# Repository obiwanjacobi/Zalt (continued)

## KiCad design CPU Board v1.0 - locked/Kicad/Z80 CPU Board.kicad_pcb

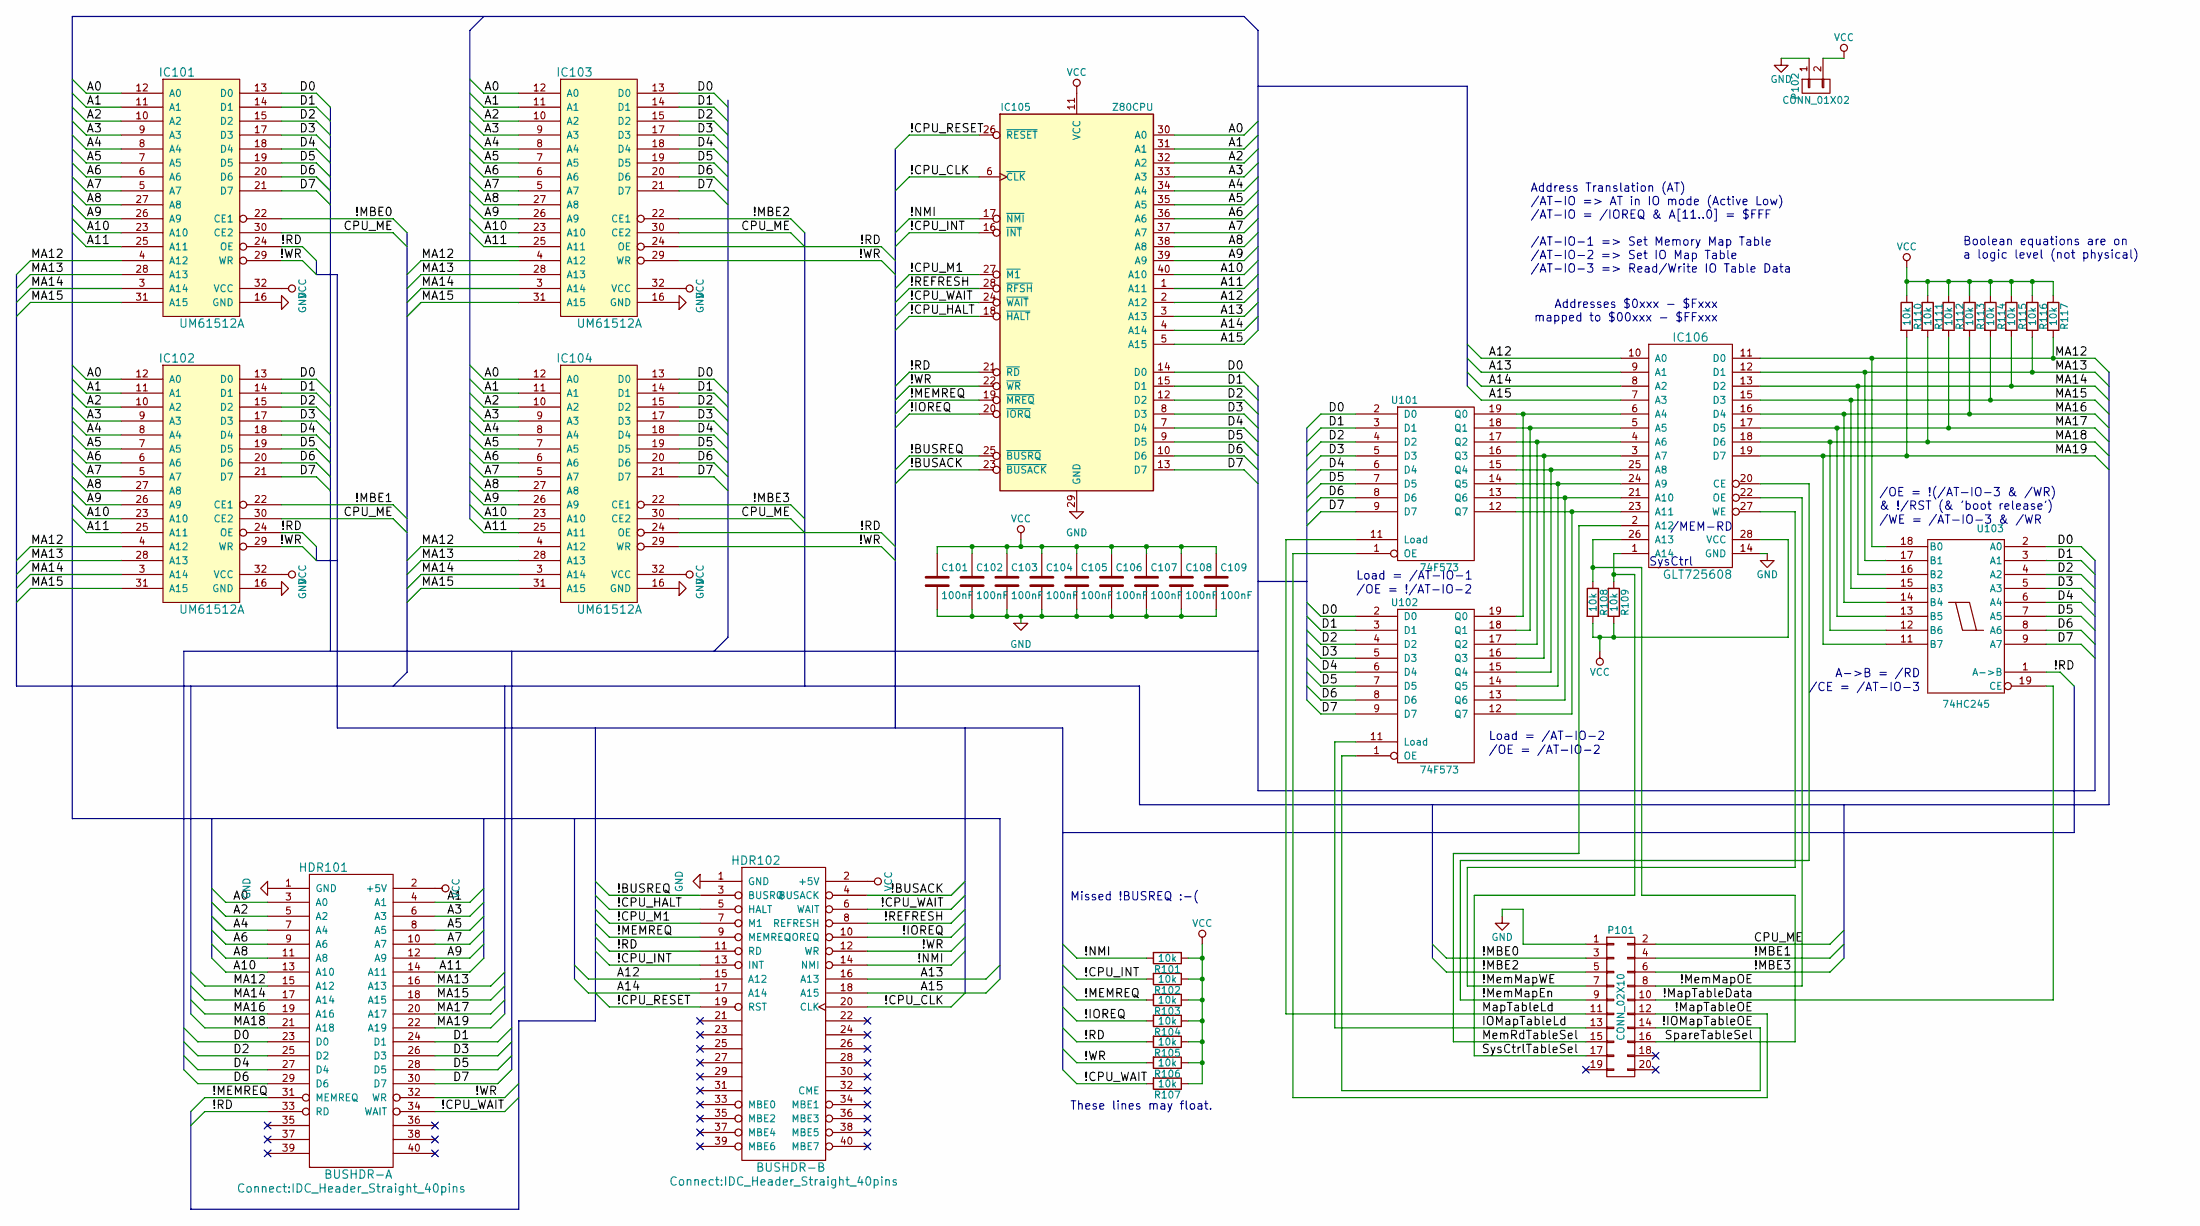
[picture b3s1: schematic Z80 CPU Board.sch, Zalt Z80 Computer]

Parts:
C101, C102, C103, C104, C105, C106, C107, C108, C109: 100nF; C_0603_HandSoldering
HDR101: BUSHDR-A; IDC_Header_Straight_40pins
HDR102: BUSHDR-B; IDC_Header_Straight_40pins
IC101, IC102, IC103, IC104: UM61512A; DIP-32_0_ELL
IC105: Z80CPU; DIP-40_W15.24mm_LongPads
IC106: GLT725608; SOIC-28_7.5x17.9mm_Pitch1.27mm
P101: CONN_02X10; Pin_Header_Straight_2x10
P102: CONN_01X02; PINHEAD1-2
R101, R102, R103, R104, R105, R106, R107, R108, R109, R110, R111, R112, R113, R114, R115, R116, R117: 10k; R_0603_HandSoldering
U101, U102: 74F573; DIP-20_W7.62mm_LongPads
U103: 74HC245; DIP-20_W7.62mm_LongPads

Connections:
/!BUSACK: HDR102.4 (BUSACK), IC105.23 (~BUSACK~)
/!BUSREQ: HDR102.3 (BUSRQ), IC105.25 (~BUSRQ~)
/!CPU_CLK: HDR102.20 (CLK), IC105.6 (~CLK~)
/!CPU_HALT: HDR102.5 (HALT), IC105.18 (~HALT~)
/!CPU_INT: HDR102.13 (INT), IC105.16 (~INT~), R102.2
/!CPU_M1: HDR102.7 (M1), IC105.27 (~M1~)
/!CPU_RESET: HDR102.19 (RST), IC105.26 (~RESET~)
/!CPU_WAIT: HDR101.34 (WAIT), HDR102.6 (WAIT), IC105.24 (~WAIT~), R107.2
/!IOMapTableOE: P101.14, U102.1 (OE)
/!IOREQ: HDR102.10 (IOREQ), IC105.20 (~IORQ~), R104.2
/!MBE0: IC101.22 (CE1), P101.3
/!MBE1: IC102.22 (CE1), P101.4
/!MBE2: IC103.22 (CE1), P101.5
/!MBE3: IC104.22 (CE1), P101.6
/!MEMREQ: HDR101.31 (MEMREQ), HDR102.9 (MEMREQ), IC105.19 (~MREQ~), R103.2
/!MapTableData: P101.10, U103.19 (CE)
/!MapTableOE: P101.12, U101.1 (OE)
/!MemMapEn: IC106.27 (WE), P101.7
/!MemMapOE: IC106.22 (OE), P101.8
/!MemMapWE: IC106.20 (CE), P101.9
/!NMI: HDR102.14 (NMI), IC105.17 (~NMI~), R101.2
/!RD: HDR101.33 (RD), HDR102.11 (RD), IC101.24 (OE), IC102.24 (OE), IC103.24 (OE), IC104.24 (OE), IC105.21 (~RD~), R105.2, U103.1 (A->B)
/!REFRESH: HDR102.8 (REFRESH), IC105.28 (~RFSH~)
/!WR: HDR101.32 (WR), HDR102.12 (WR), IC101.29 (WR), IC102.29 (WR), IC103.29 (WR), IC104.29 (WR), IC105.22 (~WR~), R106.2
/A0: HDR101.3 (A0), IC101.12 (A0), IC102.12 (A0), IC103.12 (A0), IC104.12 (A0), IC105.30 (A0)
/A1: HDR101.4 (A1), IC101.11 (A1), IC102.11 (A1), IC103.11 (A1), IC104.11 (A1), IC105.31 (A1)
/A2: HDR101.5 (A2), IC101.10 (A2), IC102.10 (A2), IC103.10 (A2), IC104.10 (A2), IC105.32 (A2)
/A3: HDR101.6 (A3), IC101.9 (A3), IC102.9 (A3), IC103.9 (A3), IC104.9 (A3), IC105.33 (A3)
/A4: HDR101.7 (A4), IC101.8 (A4), IC102.8 (A4), IC103.8 (A4), IC104.8 (A4), IC105.34 (A4)
/A5: HDR101.8 (A5), IC101.7 (A5), IC102.7 (A5), IC103.7 (A5), IC104.7 (A5), IC105.35 (A5)
/A6: HDR101.9 (A6), IC101.6 (A6), IC102.6 (A6), IC103.6 (A6), IC104.6 (A6), IC105.36 (A6)
/A7: HDR101.10 (A7), IC101.5 (A7), IC102.5 (A7), IC103.5 (A7), IC104.5 (A7), IC105.37 (A7)
/A8: HDR101.11 (A8), IC101.27 (A8), IC102.27 (A8), IC103.27 (A8), IC104.27 (A8), IC105.38 (A8)
/A9: HDR101.12 (A9), IC101.26 (A9), IC102.26 (A9), IC103.26 (A9), IC104.26 (A9), IC105.39 (A9)
/A10: HDR101.13 (A10), IC101.23 (A10), IC102.23 (A10), IC103.23 (A10), IC104.23 (A10), IC105.40 (A10)
/A11: HDR101.14 (A11), IC101.25 (A11), IC102.25 (A11), IC103.25 (A11), IC104.25 (A11), IC105.1 (A11)
/A12: HDR102.15 (A12), IC105.2 (A12), IC106.10 (A0)
/A13: HDR102.16 (A13), IC105.3 (A13), IC106.9 (A1)
/A14: HDR102.17 (A14), IC105.4 (A14), IC106.8 (A2)
/A15: HDR102.18 (A15), IC105.5 (A15), IC106.7 (A3)
/CPU_ME: IC101.30 (CE2), IC102.30 (CE2), IC103.30 (CE2), IC104.30 (CE2), P101.2
/D0: HDR101.23 (D0), IC101.13 (D0), IC102.13 (D0), IC103.13 (D0), IC104.13 (D0), IC105.14 (D0), U101.2 (D0), U102.2 (D0), U103.2 (A0)
/D1: HDR101.24 (D1), IC101.14 (D1), IC102.14 (D1), IC103.14 (D1), IC104.14 (D1), IC105.15 (D1), U101.3 (D1), U102.3 (D1), U103.3 (A1)
/D2: HDR101.25 (D2), IC101.15 (D2), IC102.15 (D2), IC103.15 (D2), IC104.15 (D2), IC105.12 (D2), U101.4 (D2), U102.4 (D2), U103.4 (A2)
/D3: HDR101.26 (D3), IC101.17 (D3), IC102.17 (D3), IC103.17 (D3), IC104.17 (D3), IC105.8 (D3), U101.5 (D3), U102.5 (D3), U103.5 (A3)
/D4: HDR101.27 (D4), IC101.18 (D4), IC102.18 (D4), IC103.18 (D4), IC104.18 (D4), IC105.7 (D4), U101.6 (D4), U102.6 (D4), U103.6 (A4)
/D5: HDR101.28 (D5), IC101.19 (D5), IC102.19 (D5), IC103.19 (D5), IC104.19 (D5), IC105.9 (D5), U101.7 (D5), U102.7 (D5), U103.7 (A5)
/D6: HDR101.29 (D6), IC101.20 (D6), IC102.20 (D6), IC103.20 (D6), IC104.20 (D6), IC105.10 (D6), U101.8 (D6), U102.8 (D6), U103.8 (A6)
/D7: HDR101.30 (D7), IC101.21 (D7), IC102.21 (D7), IC103.21 (D7), IC104.21 (D7), IC105.13 (D7), U101.9 (D7), U102.9 (D7), U103.9 (A7)
/IOMapTableLd: P101.13, U102.11 (Load)
/MA12: HDR101.15 (A12), IC101.4 (A12), IC102.4 (A12), IC103.4 (A12), IC104.4 (A12), IC106.11 (D0), R117.2, U103.18 (B0)
/MA13: HDR101.16 (A13), IC101.28 (A13), IC102.28 (A13), IC103.28 (A13), IC104.28 (A13), IC106.12 (D1), R116.2, U103.17 (B1)
/MA14: HDR101.17 (A14), IC101.3 (A14), IC102.3 (A14), IC103.3 (A14), IC104.3 (A14), IC106.13 (D2), R115.2, U103.16 (B2)
/MA15: HDR101.18 (A15), IC101.31 (A15), IC102.31 (A15), IC103.31 (A15), IC104.31 (A15), IC106.15 (D3), R114.2, U103.15 (B3)
/MA16: HDR101.19 (A16), IC106.16 (D4), R113.2, U103.14 (B4)
/MA17: HDR101.20 (A17), IC106.17 (D5), R112.2, U103.13 (B5)
/MA18: HDR101.21 (A18), IC106.18 (D6), R111.2, U103.12 (B6)
/MA19: HDR101.22 (A19), IC106.19 (D7), R110.2, U103.11 (B7)
/MapTableLd: P101.11, U101.11 (Load)
/MemRdTableSel: IC106.2 (A12), P101.15
/SpareTableSel: IC106.26 (A13), P101.16, R108.1
/SysCtrlTableSel: IC106.1 (A14), P101.17, R109.1
GND: C101.2, C102.2, C103.2, C104.2, C105.2, C106.2, C107.2, C108.2, C109.2, HDR101.1 (GND), HDR102.1 (GND), IC101.16 (GND), IC102.16 (GND), IC103.16 (GND), IC104.16 (GND), IC105.29 (GND), IC106.14 (GND), P101.1, P102.1, U101.10 (GND), U102.10 (GND), U103.10 (GND)
unnamed: IC106.3 (A7), U101.16 (Q3), U102.16 (Q3)
unnamed: IC106.4 (A6), U101.17 (Q2), U102.17 (Q2)
unnamed: IC106.5 (A5), U101.18 (Q1), U102.18 (Q1)
unnamed: IC106.6 (A4), U101.19 (Q0), U102.19 (Q0)
unnamed: IC106.21 (A10), U101.13 (Q6), U102.13 (Q6)
unnamed: IC106.23 (A11), U101.12 (Q7), U102.12 (Q7)
unnamed: IC106.24 (A9), U101.14 (Q5), U102.14 (Q5)
unnamed: IC106.25 (A8), U101.15 (Q4), U102.15 (Q4)
VCC: C101.1, C102.1, C103.1, C104.1, C105.1, C106.1, C107.1, C108.1, C109.1, HDR101.2 (+5V), HDR102.2 (+5V), IC101.32 (VCC), IC102.32 (VCC), IC103.32 (VCC), IC104.32 (VCC), IC105.11 (VCC), IC106.28 (VCC), P102.2, R101.1, R102.1, R103.1, R104.1, R105.1, R106.1, R107.1, R108.2, R109.2, R110.1, R111.1, R112.1, R113.1, R114.1, R115.1, R116.1, R117.1, U101.20 (VCC), U102.20 (VCC), U103.20 (VCC)

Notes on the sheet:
Addresses $0xxx - $Fxxx mapped to $00xxx - $FFxxx
Address Translation (AT) /AT-IO => AT in IO mode (Active Low) /AT-IO = /IOREQ & A[11..0] = $FFF /AT-IO-1 => Set Memory Map Table /AT-IO-2 => Set IO Map Table /AT-IO-3 => Read/Write IO Table Data
A->B = /RD
/CE = /AT-IO-3
/OE = !(/AT-IO-3 & /WR) & !/RST (& 'boot release')
/WE = /AT-IO-3 & /WR
/MEM-RD
SysCtrl
Load = /AT-IO-2
/OE = /AT-IO-2
Boolean equations are on a logic level (not physical)
Load = /AT-IO-1
/OE = !/AT-IO-2
These lines may float.
Missed !BUSREQ :-(

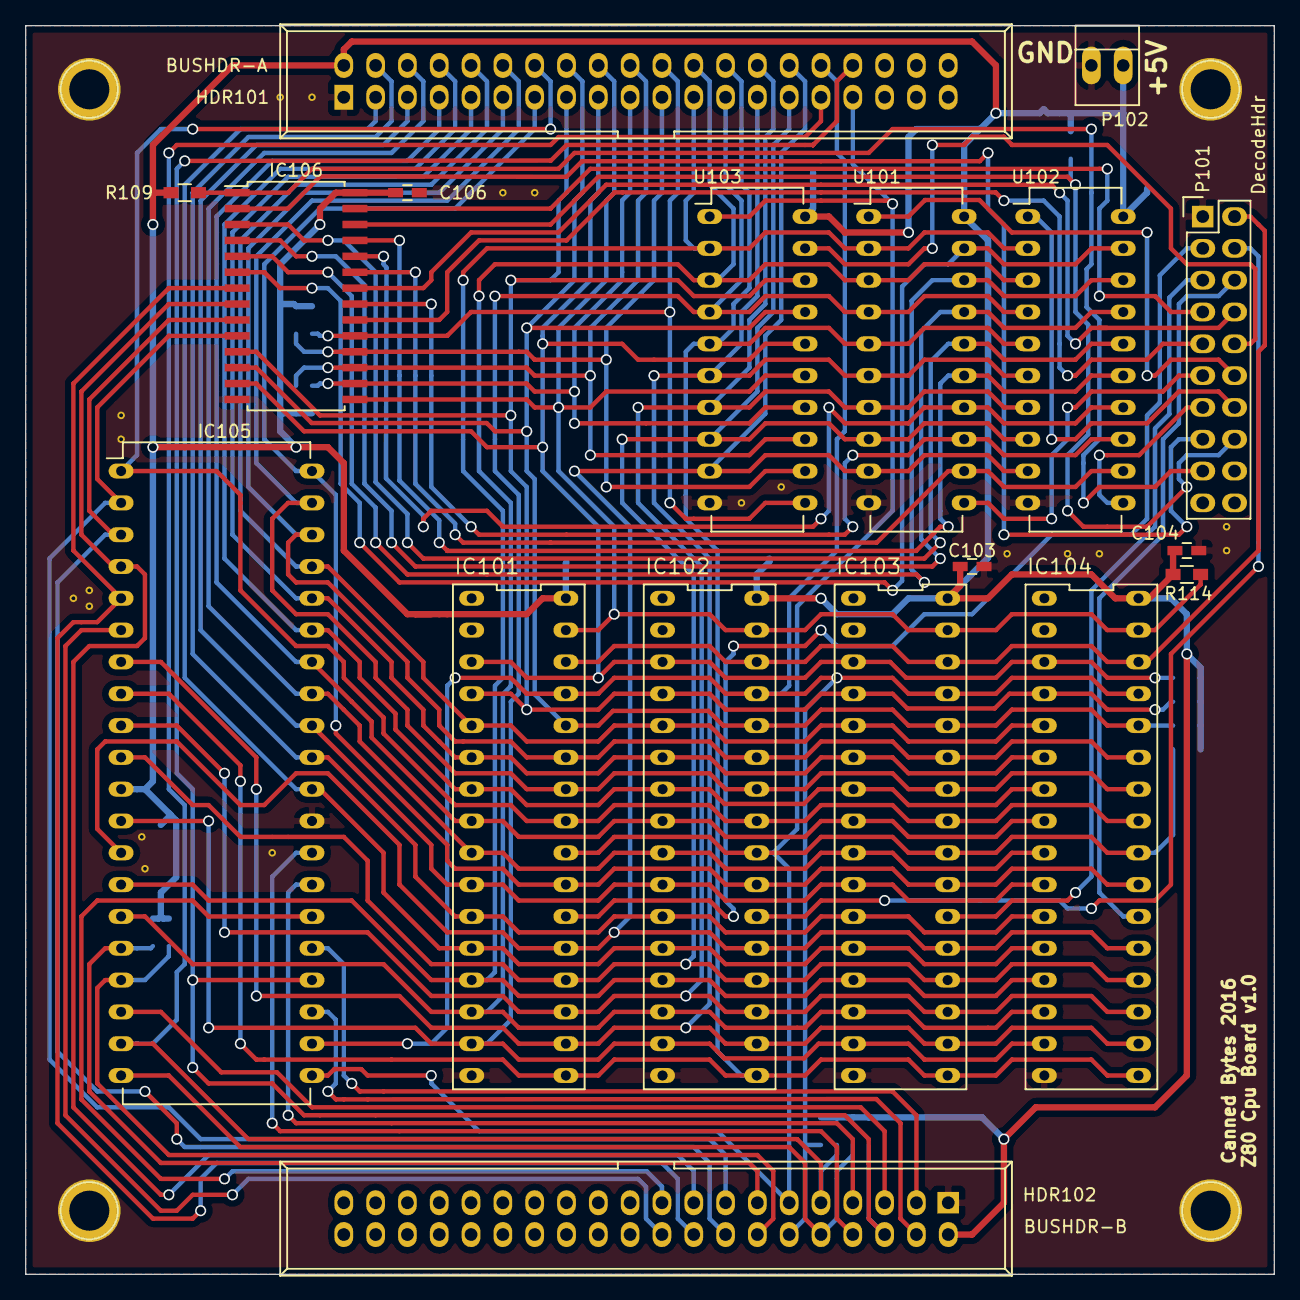
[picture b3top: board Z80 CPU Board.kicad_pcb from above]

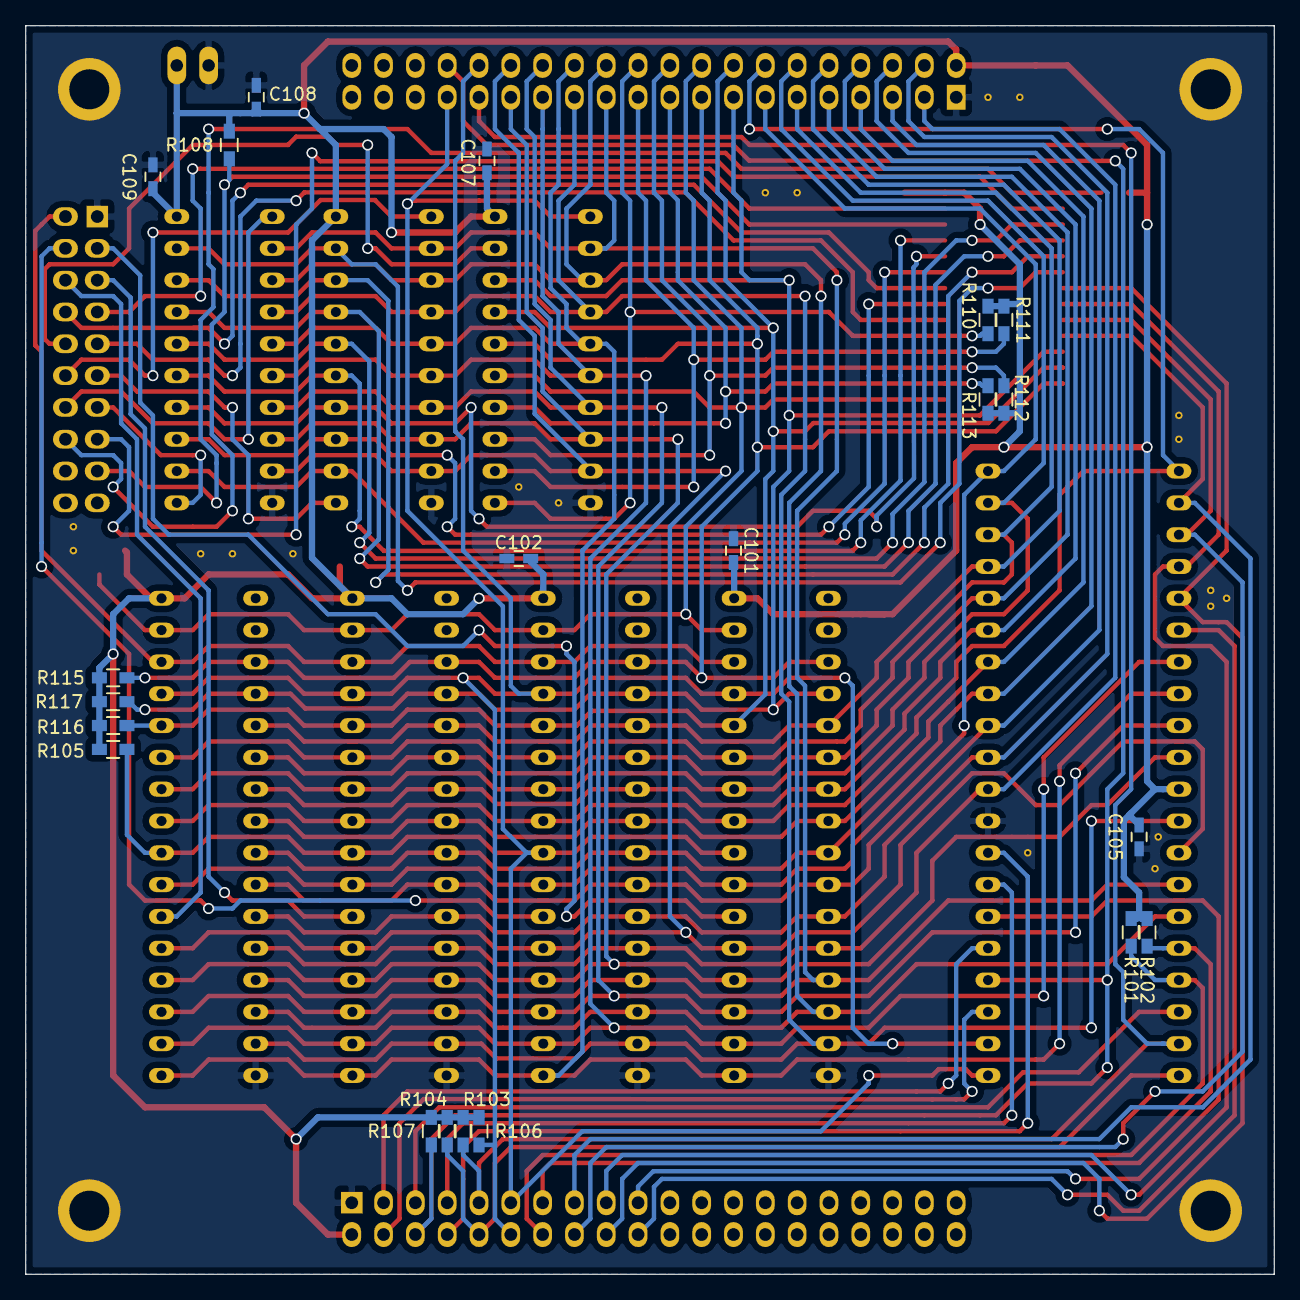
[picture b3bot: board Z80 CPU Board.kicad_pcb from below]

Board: 2 copper layers, 99.7 x 99.7 mm, 39 parts (21 on the bottom side), 72 nets.

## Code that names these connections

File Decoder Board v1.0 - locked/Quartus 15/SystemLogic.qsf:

# -------------------------------------------------------------------------- #
#
# Copyright (C) 1991-2015 Altera Corporation. All rights reserved.
# Your use of Altera Corporation's design tools, logic functions 
# and other software and tools, and its AMPP partner logic 
# functions, and any output files from any of the foregoing 
# (including device programming or simulation files), and any 
# associated documentation or information are expressly subject 
# to the terms and conditions of the Altera Program License 
# Subscription Agreement, the Altera Quartus Prime License Agreement,
# the Altera MegaCore Function License Agreement, or other 
# applicable license agreement, including, without limitation, 
# that your use is for the sole purpose of programming logic 
# devices manufactured by Altera and sold by Altera or its 
# authorized distributors.  Please refer to the applicable 
# agreement for further details.
#
# -------------------------------------------------------------------------- #
#
# Quartus Prime
# Version 15.1.0 Build 185 10/21/2015 SJ Lite Edition
# Date created = 08:41:50  December 29, 2015
#
# -------------------------------------------------------------------------- #
#
# Notes:
#
# 1) The default values for assignments are stored in the file:
#		SystemLogic_assignment_defaults.qdf
#    If this file doesn't exist, see file:
#		assignment_defaults.qdf
#
# 2) Altera recommends that you do not modify this file. This
#    file is updated automatically by the Quartus Prime software
#    and any changes you make may be lost or overwritten.
#
# -------------------------------------------------------------------------- #


set_global_assignment -name FAMILY "MAX II"
set_global_assignment -name DEVICE EPM240T100C5
set_global_assignment -name TOP_LEVEL_ENTITY SystemLogic
set_global_assignment -name ORIGINAL_QUARTUS_VERSION 15.1.0
set_global_assignment -name PROJECT_CREATION_TIME_DATE "08:41:50  DECEMBER 29, 2015"
set_global_assignment -name LAST_QUARTUS_VERSION 15.0.0
set_global_assignment -name PROJECT_OUTPUT_DIRECTORY output_files
set_global_assignment -name MIN_CORE_JUNCTION_TEMP 0
set_global_assignment -name MAX_CORE_JUNCTION_TEMP 85
set_global_assignment -name ERROR_CHECK_FREQUENCY_DIVISOR "-1"
set_global_assignment -name POWER_EXT_SUPPLY_VOLTAGE_TO_REGULATOR 3.3V
set_global_assignment -name EDA_SIMULATION_TOOL "ModelSim-Altera (VHDL)"
set_global_assignment -name EDA_OUTPUT_DATA_FORMAT VHDL -section_id eda_simulation
set_global_assignment -name STRATIX_DEVICE_IO_STANDARD "3.3-V LVTTL"
set_global_assignment -name DEVICE_FILTER_PACKAGE TQFP
set_global_assignment -name VHDL_FILE SystemLogic.vhd
set_global_assignment -name VHDL_FILE MemoryController.vhd
set_global_assignment -name POWER_PRESET_COOLING_SOLUTION "NO HEAT SINK WITH STILL AIR"
set_global_assignment -name DEVICE_FILTER_PIN_COUNT 100
set_location_assignment PIN_100 -to a[0]
set_location_assignment PIN_99 -to a[1]
set_location_assignment PIN_98 -to a[2]
set_location_assignment PIN_97 -to a[3]
set_location_assignment PIN_96 -to a[4]
set_location_assignment PIN_95 -to a[5]
set_location_assignment PIN_92 -to a[6]
set_location_assignment PIN_91 -to a[7]
set_location_assignment PIN_90 -to a[8]
set_location_assignment PIN_89 -to a[9]
set_location_assignment PIN_88 -to a[10]
set_location_assignment PIN_87 -to a[11]
set_location_assignment PIN_18 -to a[12]
set_location_assignment PIN_17 -to a[13]
set_location_assignment PIN_16 -to a[14]
set_location_assignment PIN_15 -to a[15]
set_location_assignment PIN_86 -to ma[0]
set_location_assignment PIN_85 -to ma[1]
set_location_assignment PIN_84 -to ma[2]
set_location_assignment PIN_83 -to ma[3]
set_location_assignment PIN_82 -to ma[4]
set_location_assignment PIN_81 -to ma[5]
set_location_assignment PIN_78 -to ma[6]
set_location_assignment PIN_77 -to ma[7]
set_location_assignment PIN_12 -to clk
set_location_assignment PIN_75 -to ctrl[1]
set_location_assignment PIN_76 -to ctrl[0]
set_location_assignment PIN_55 -to io_ex[0]
set_location_assignment PIN_37 -to io_ex[16]
set_location_assignment PIN_38 -to io_ex[15]
set_location_assignment PIN_39 -to io_ex[14]
set_location_assignment PIN_40 -to io_ex[13]
set_location_assignment PIN_41 -to io_ex[12]
set_location_assignment PIN_42 -to io_ex[11]
set_location_assignment PIN_43 -to io_ex[10]
set_location_assignment PIN_44 -to io_ex[9]
set_location_assignment PIN_47 -to io_ex[8]
set_location_assignment PIN_48 -to io_ex[7]
set_location_assignment PIN_49 -to io_ex[6]
set_location_assignment PIN_50 -to io_ex[5]
set_location_assignment PIN_51 -to io_ex[4]
set_location_assignment PIN_52 -to io_ex[3]
set_location_assignment PIN_53 -to io_ex[2]
set_location_assignment PIN_54 -to io_ex[1]
set_location_assignment PIN_66 -to memmapld
set_location_assignment PIN_58 -to memrdtablesel
set_location_assignment PIN_35 -to n_busack
set_location_assignment PIN_36 -to n_busreq
set_location_assignment PIN_34 -to n_cpuhalt
set_location_assignment PIN_30 -to n_cpum1
set_location_assignment PIN_33 -to n_cpuwait
set_location_assignment PIN_29 -to n_cpurefresh
set_location_assignment PIN_20 -to n_cpuint
set_location_assignment PIN_19 -to n_cpunmi
set_location_assignment PIN_27 -to n_ioreq
set_location_assignment PIN_28 -to n_memreq
set_location_assignment PIN_26 -to n_rd
set_location_assignment PIN_14 -to n_reset
set_location_assignment PIN_21 -to n_wr
set_location_assignment PIN_62 -to iomemmapld
set_location_assignment PIN_61 -to n_iomaptableoe
set_location_assignment PIN_67 -to n_maptabledata
set_location_assignment PIN_64 -to n_maptableoe
set_location_assignment PIN_71 -to n_mbe[3]
set_location_assignment PIN_72 -to n_mbe[2]
set_location_assignment PIN_73 -to n_mbe[1]
set_location_assignment PIN_74 -to n_mbe[0]
set_location_assignment PIN_68 -to n_memmapen
set_location_assignment PIN_69 -to n_memmapoe
set_location_assignment PIN_70 -to n_memmapwe
set_location_assignment PIN_57 -to sparetablesel
set_location_assignment PIN_56 -to sysctrltablesel
set_location_assignment PIN_1 -to io[7]
set_location_assignment PIN_2 -to io[6]
set_location_assignment PIN_3 -to io[5]
set_location_assignment PIN_4 -to io[4]
set_location_assignment PIN_5 -to io[3]
set_location_assignment PIN_6 -to io[2]
set_location_assignment PIN_7 -to io[1]
set_location_assignment PIN_8 -to io[0]
set_global_assignment -name VHDL_FILE MemoryDecoder.vhd
set_global_assignment -name VHDL_FILE TestMemoryDecoder.vhd
set_global_assignment -name CDF_FILE output_files/SystemLogic.cdf

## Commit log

2016-10-12 Initial publication of Zalt Z80 computer source files.
2016-10-16 Documented lifted caps on PSoC5 kit.
2016-10-21 Added schematics as pdf for general viewing.
2016-12-12 HelloWorld integration test working.
2016-12-13 Cleanup
2016-12-23 Added integration tests. Setup vscode for developing z88dk target further and moved some bios files into place.
2016-12-26 Added Heap and RingBuffer initial code and tests.
2016-12-28 More coding towards a monitor
2016-12-30 Working toward a simple monitor (Z80).
2017-01-04 Started with Z80 zalt system code and added Z80 interrupt handling to PSoC.
2017-01-06 Added debugger and breakpoint functionality.
2017-01-08 Interrupts (keyboard) are starting to work.
2017-01-25 Added a VirtualDevices app for handling USB on the PC side. Added UsbProcessor to the PSoC for handling USB on Zalt. Implemented keyboard over USB.
2017-02-18 Zalt Virtual Devices and start of GPU design,
2017-03-01 Added usb-test roundtrip message support.
2018-01-14 Resurrected custom part libs from .bak files and relinked them in the schematic.
2018-02-03 Restored Kicad library files that were missing.
2018-02-03 Added libusb binaries (windows).
2018-02-03 Reformatted and updated readme.md
2018-02-03 After seeing readme.md in guthub...
2018-02-03 that didn't work...
2018-02-03 Oops.
2018-12-13 async
2018-12-13 fixes and build task
2018-12-13 async fixes
2018-12-13 debug guards
2018-12-14 asm DEBUG defs
2018-12-14 update root readme
2018-12-14 char_t unsigned
2018-12-14 tweaking
2018-12-17 getting it to work again
2018-12-18 unit tests Async
2018-12-18 Error unit tests
2018-12-19 test tweaking
2018-12-19 fix build
2018-12-19 string tests and fixes
2018-12-19 heap tests
2018-12-19 io tests
2018-12-19 stream test
2018-12-19 tweaks
2018-12-20 more stream tests
2018-12-21 restoring old character port
2018-12-22 preprocessing m4 files
2018-12-22 asm symbol error fix
2018-12-22 build script tweaks
2018-12-22 docs
2018-12-23 updated helloworld test with new lib code
2018-12-23 bin files cleanup
2018-12-23 asm noodling
2018-12-23 settings
2018-12-23 zalt_c lib
2018-12-23 clean bin from test
2018-12-24 simplified lib cmd line
2018-12-24 virtual devices compiles
2018-12-24 getting usb working
2018-12-25 cleanup and tests
2018-12-25 terminal texts
2018-12-25 mm commands
2018-12-25 sysctrl status cmd
2018-12-25 stat docs
2018-12-25 todos
2018-12-26 build script tweaking
2018-12-26 moved bios vars into system data section
2018-12-26 refactor bios asm
2018-12-29 getting memory manager to work + dz80
2018-12-29 Redraw of SystemController and added MMU sync
2018-12-29 MMU pop and fix
2018-12-29 dz80 exe
2018-12-29 rel ptr
2018-12-30 relptr fix
2018-12-30 compiles sccz80
2018-12-31 memory manager and debugger
2018-12-31 unit test fixes
2019-01-01 crt m4 fails
2019-01-01 this does not work either
2019-01-01 file paths ok
2019-01-01 works
2019-01-01 build
2019-01-01 sccz80 build fix
2019-01-02 moved debug regs to data
2019-01-02 md cmd
2019-01-02 made SetPageAt callee
2019-01-02 compiler directives simplification
2019-01-04 MemoryManager_Init
2019-01-04 memory manager names consistent
2019-01-06 memmgr u101 latch timing issue
2019-01-09 humble far mem beginnings
2019-01-10 write far mem
2019-01-12 memory flags
2019-01-12 more debug stuff
2019-05-03 Kicad libs
2019-05-03 todo
2019-05-03 Character VGA
2019-05-03 small stuff
2019-05-03 Zalt to ISA
2019-05-05 Sort of working version
2019-10-23 update (images)
2020-01-30 wait for busack and pin macro
2020-01-30 terminal prompt and simpler newline handling
2020-02-11 parser simplification
2020-02-11 TTL VGA
2020-02-12 more sheets in schematic
2020-02-12 horizontal and vertical decoder updates
2020-02-14 binary counter cupl
2020-02-14 readme
2020-02-23 updates to 'working' version
2020-03-08 vga memory interface
2020-03-21 vga test code
2020-03-26 getting stuff working again
2020-05-02 vga work
2020-05-03 More VGA work
2020-05-11 TTL VGA v0.2
2020-05-12 video bit mux
2020-05-13 video mode mux
2020-12-06 update kicad
2020-12-20 Restructure
2020-12-23 progress
2020-12-24 finishing
2020-12-26 VDP in production
2021-01-03 prototype
2021-01-17 Ide working prototype
2021-01-27 Ide prototype
2021-02-07 atmega ide controller
2024-04-06 gitiggnore
2024-04-06 fixes
2026-03-26 chat with claude
2026-03-26 new simpler build structure
2026-03-26 async stream spike
2026-03-28 moved source 2 to zalt2
